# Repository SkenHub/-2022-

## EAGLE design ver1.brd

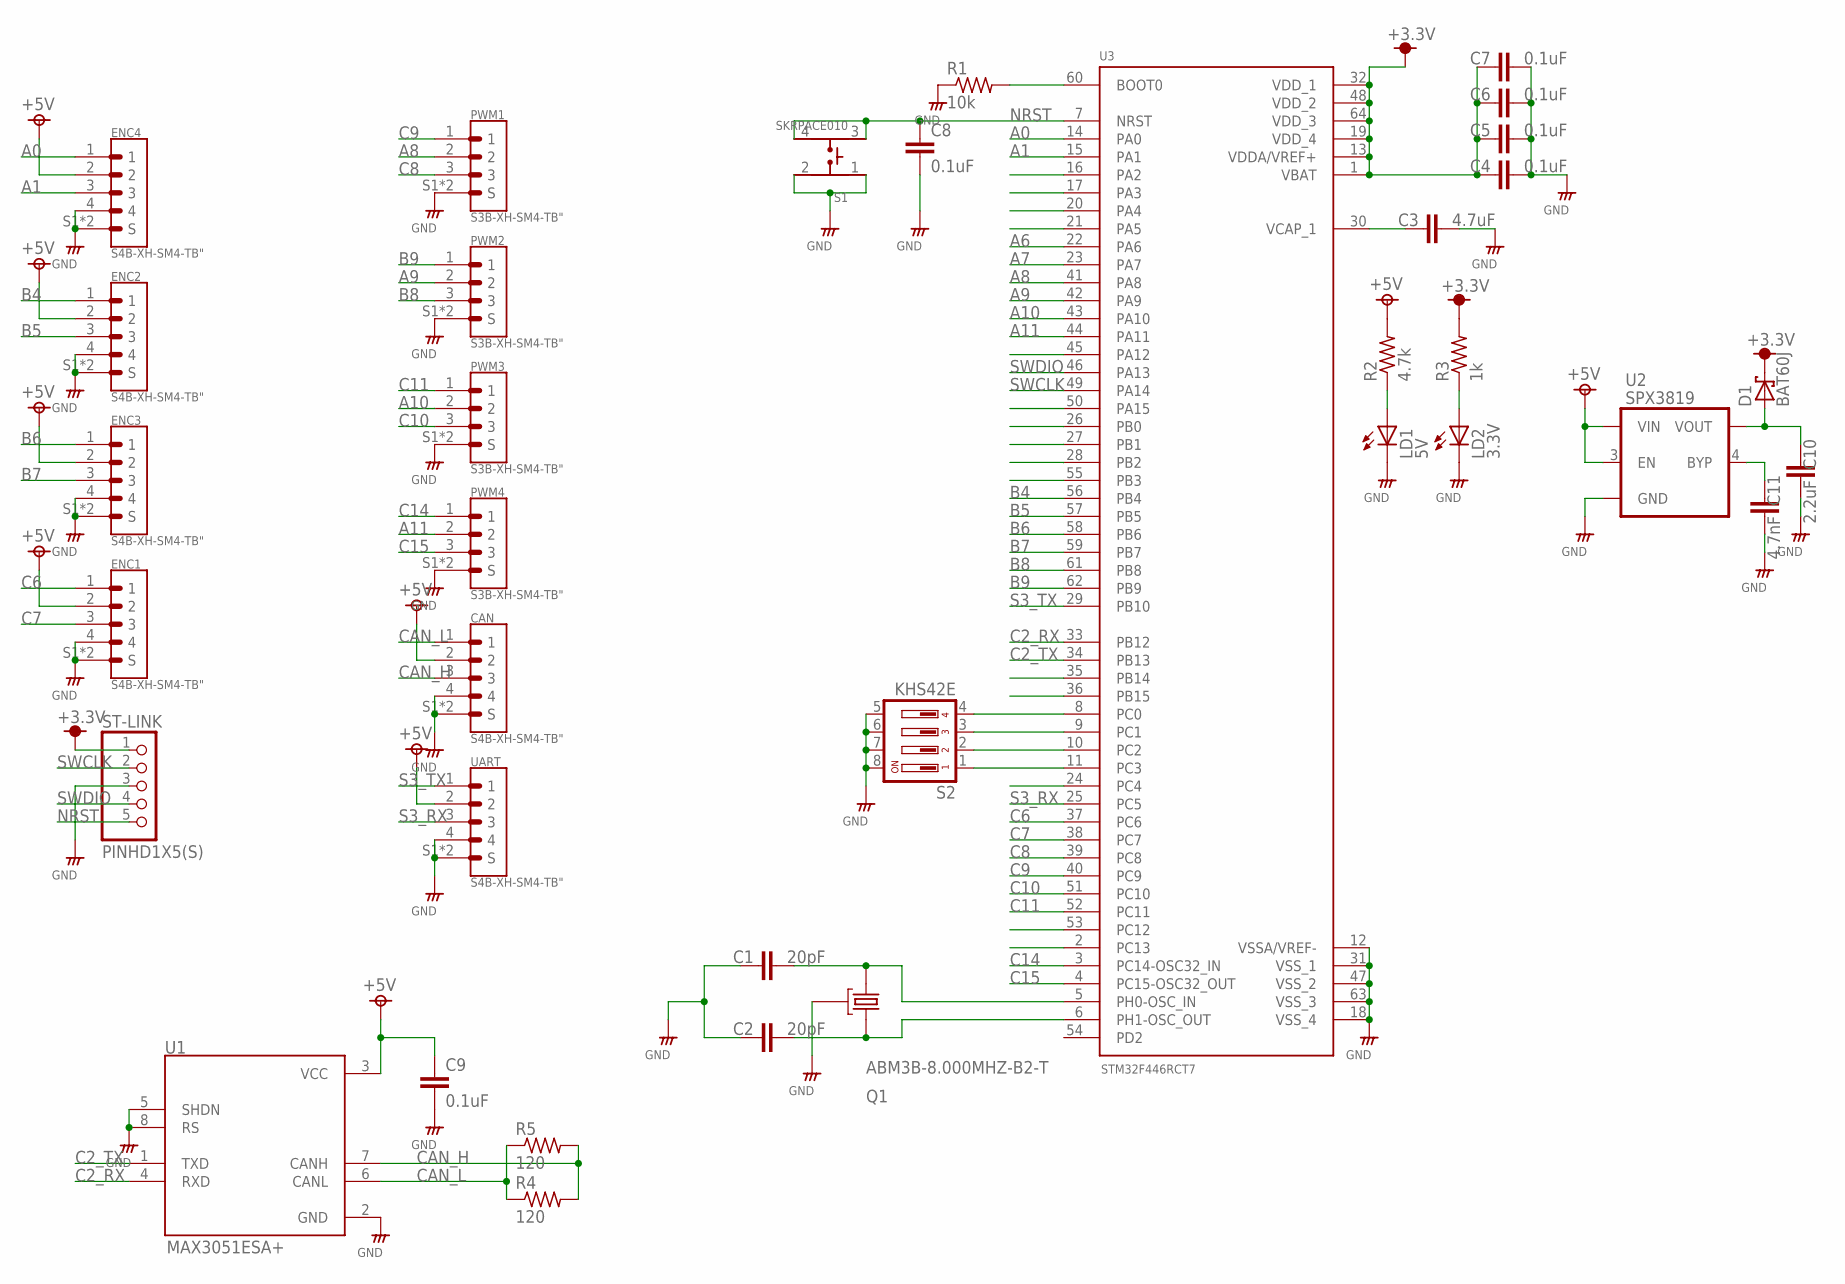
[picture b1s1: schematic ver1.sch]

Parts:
C1, C2: 20pF; C0603
C3: 4.7uF; C0805
C4, C5, C6, C7: 0.1uF; C0805
C8, C9: 0.1uF; C0603
C10: 2.2uF; C0603
C11: 4.7nF; C0603
CAN: S4B-XH-SM4-TB"; S4B-XH-SM4-TB
D1: BAT60J; SOD323_ST
ENC1, ENC2, ENC3, ENC4: S4B-XH-SM4-TB"; S4B-XH-SM4-TB
LD1: 5V; CHIP-LED3216
LD2: 3.3V; CHIP-LED3216
PWM1, PWM2, PWM3, PWM4: S3B-XH-SM4-TB"; S3B-XH-SM4-TB
Q1: ABM3B-8.000MHZ-B2-T; OSCCC500X320X110-4N
R1: 10k; R0603
R2: 4.7k; R0603
R3: 1k; R0603
R4, R5: 120; R0603
S1: SKRPACE010; SW_SKRPACE010
S2: KHS42E
ST-LINK: PINHD1X5(S); 1X5(XH_S)
U1: MAX3051ESA+; SOIC127P600X175-8N
U2: SPX3819; SOT23-5
U3: STM32F446RCT7; QFP50P1200X1200X160-64N
UART: S4B-XH-SM4-TB"; S4B-XH-SM4-TB

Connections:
+3V3: C4.1, C5.1, C6.1, C7.1, D1.C, R3.2, ST-LINK.1, U3.1 (VBAT), U3.13 (VDDA/VREF+), U3.19 (VDD_4), U3.32 (VDD_1), U3.48 (VDD_2), U3.64 (VDD_3)
+5V: C9.1, CAN.2, ENC1.2, ENC2.2, ENC3.2, ENC4.2, R2.2, U1.3 (VCC), U2.1 (VIN), U2.3 (EN), UART.2
A0: ENC4.1, U3.14 (PA0)
A1: ENC4.3, U3.15 (PA1)
A6: U3.22 (PA6)
A7: U3.23 (PA7)
A8: PWM1.2, U3.41 (PA8)
A9: PWM2.2, U3.42 (PA9)
A10: PWM3.2, U3.43 (PA10)
A11: PWM4.2, U3.44 (PA11)
B4: ENC2.1, U3.56 (PB4)
B5: ENC2.3, U3.57 (PB5)
B6: ENC3.1, U3.58 (PB6)
B7: ENC3.3, U3.59 (PB7)
B8: PWM2.3, U3.61 (PB8)
B9: PWM2.1, U3.62 (PB9)
C2_RX: U1.4 (RXD), U3.33 (PB12)
C2_TX: U1.1 (TXD), U3.34 (PB13)
C6: ENC1.1, U3.37 (PC6)
C7: ENC1.3, U3.38 (PC7)
C8: PWM1.3, U3.39 (PC8)
C9: PWM1.1, U3.40 (PC9)
C10: PWM3.3, U3.51 (PC10)
C11: PWM3.1, U3.52 (PC11)
C14: PWM4.1, U3.3 (PC14-OSC32_IN)
C15: PWM4.3, U3.4 (PC15-OSC32_OUT)
CAN_H: CAN.3, R4.2, R5.2, U1.7 (CANH)
CAN_L: CAN.1, R4.1, R5.1, U1.6 (CANL)
GND: C1.1, C2.1, C3.2, C4.2, C5.2, C6.2, C7.2, C8.2, C9.2, C10.2, C11.2, CAN.4, CAN.S1 (S), CAN.S2 (S), ENC1.4, ENC1.S1 (S), ENC1.S2 (S), ENC2.4, ENC2.S1 (S), ENC2.S2 (S), ENC3.4, ENC3.S1 (S), ENC3.S2 (S), ENC4.4, ENC4.S1 (S), ENC4.S2 (S), LD1.C, LD2.C, PWM1.S1 (S), PWM1.S2 (S), PWM2.S1 (S), PWM2.S2 (S), PWM3.S1 (S), PWM3.S2 (S), PWM4.S1 (S), PWM4.S2 (S), Q1.2 (GND), Q1.4 (GND), R1.1, S1.1, S1.2, S2.5, S2.6, S2.7, S2.8, ST-LINK.3, U1.2 (GND), U1.5 (SHDN), U1.8 (RS), U2.2 (GND), U3.12 (VSSA/VREF-), U3.18 (VSS_4), U3.31 (VSS_1), U3.47 (VSS_2), U3.63 (VSS_3), UART.4, UART.S1 (S), UART.S2 (S)
unnamed: C1.2, Q1.1, U3.5 (PH0-OSC_IN)
unnamed: C2.2, Q1.3, U3.6 (PH1-OSC_OUT)
unnamed: R1.2, U3.60 (BOOT0)
unnamed: C3.1, U3.30 (VCAP_1)
unnamed: LD1.A, R2.1
unnamed: LD2.A, R3.1
unnamed: C11.1, U2.4 (BYP)
unnamed: C10.1, D1.A, U2.5 (VOUT)
unnamed: S2.4, U3.8 (PC0)
unnamed: S2.3, U3.9 (PC1)
unnamed: S2.2, U3.10 (PC2)
unnamed: S2.1, U3.11 (PC3)
NRST: C8.1, S1.3, S1.4, ST-LINK.5, U3.7 (NRST)
S3_RX: U3.25 (PC5), UART.3
S3_TX: U3.29 (PB10), UART.1
SWCLK: ST-LINK.2, U3.49 (PA14)
SWDIO: ST-LINK.4, U3.46 (PA13)

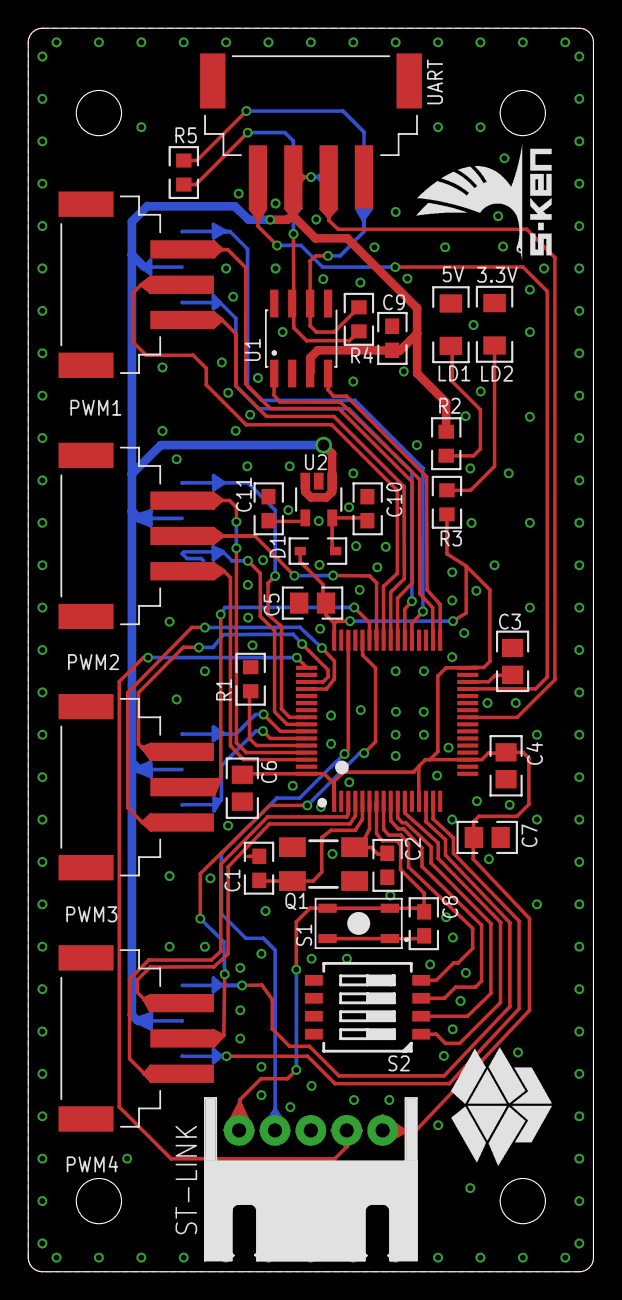
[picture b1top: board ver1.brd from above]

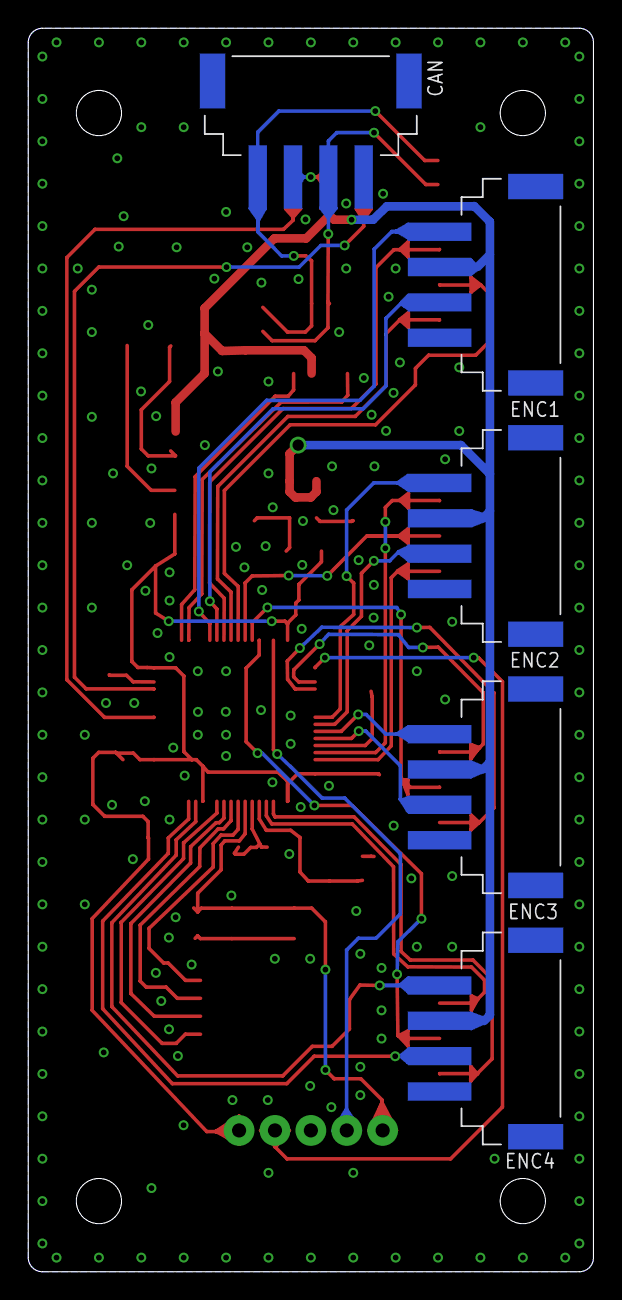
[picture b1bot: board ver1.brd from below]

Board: 2 copper layers, 40.0 x 88.0 mm, 38 parts (5 on the bottom side), 44 nets.

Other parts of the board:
U$3: SKEN_LOGO
U$4: BLACK_BOX
